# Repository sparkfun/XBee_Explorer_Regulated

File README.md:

XBee Explorer Regulated
=======================

*[XBee Explorer Regulated (WRL-11373)](https://www.sparkfun.com/products/11373)*
 
 This Explorer regulates 5V serial signals to 3.3V to enable communication with the XBee modules.
 This model works with all XBee modules, including Series 1 and 2, standard and Pro versions. 
 
Repository Contents
-------------------

* **/Hardware** - All Eagle design files (.brd, .sch)

License Information
-------------------
The hardware is released under [Creative Commons ShareAlike 4.0 International](https://creativecommons.org/licenses/by-sa/4.0/).
The code is beerware; if you see me (or any other SparkFun employee) at the local, and you've found our code helpful, please buy us a round!

Distributed as-is; no warranty is given.

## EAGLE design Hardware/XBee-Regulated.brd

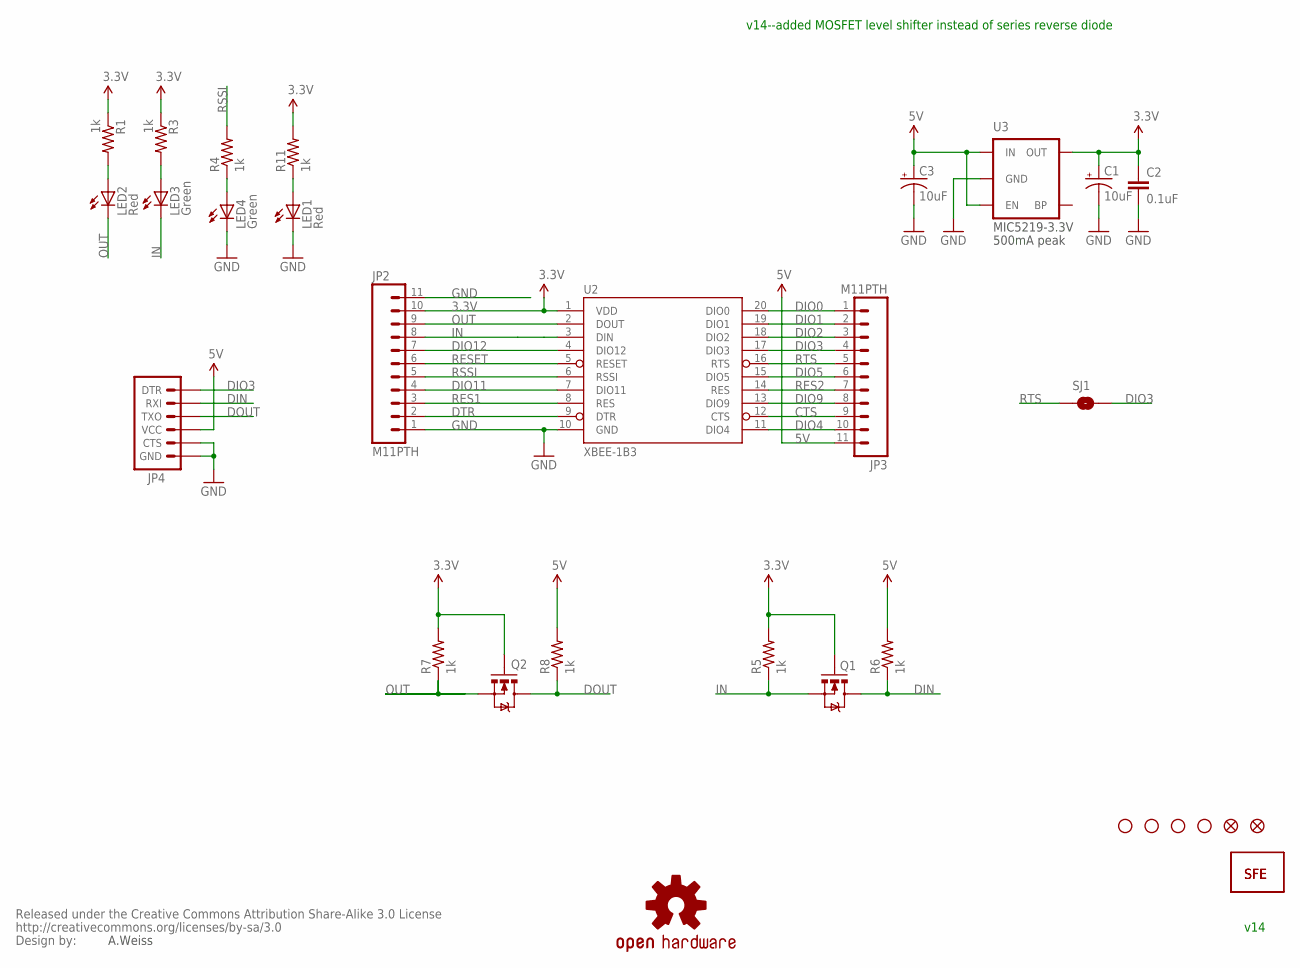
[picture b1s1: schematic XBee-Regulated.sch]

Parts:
C1, C3: 10uF; EIA3216
C2: 0.1uF; 0402-CAP
JP2, JP3: M11PTH; 1X11
JP4: ARDUINO_SERIAL_PROGRAMPTH; 1X06
LED1, LED2: Red; LED-0603
LED3, LED4: Green; LED-0603
Q1, Q2: MOSFET-NCHANNELSMD; SOT23-3
R1, R3, R4, R5, R6, R7, R8, R11: 1k; 0402-RES
SJ1: SOLDERJUMPERNO; SJ_2S-NO
U2: XBEE-1B3; XBEE-SMD
U3: V_REG_LDOSMD; SOT23-5
U$1: LOGO-SFESK; SFE-LOGO-FLAME
U$3: OSHW-LOGOS; OSHW-LOGO-S
U$4: LOGO-SFENEW; SFE-NEW-WEBLOGO
U$5, U$9, U$10, U$11: STAND-OFF
U$7, U$16: FIDUCIAL1X2; FIDUCIAL-1X2
U$8: CREATIVE_COMMONS

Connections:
3.3V: C1.A (+), C2.1, JP2.10, Q1.1 (G), Q2.1 (G), R1.1, R3.1, R5.2, R7.2, R11.2, U2.1 (VDD), U3.5 (OUT)
5V: C3.A (+), JP3.11, JP4.4 (VCC), R6.2, R8.2, U3.1 (IN), U3.3 (EN)
CTS: JP3.9, U2.12 (CTS)
DIN: JP4.2 (RXI), Q1.3 (D), R6.1
DIO0: JP3.1, U2.20 (DIO0)
DIO1: JP3.2, U2.19 (DIO1)
DIO2: JP3.3, U2.18 (DIO2)
DIO3: JP3.4, JP4.1 (DTR), SJ1.2, U2.17 (DIO3)
DIO4: JP3.10, U2.11 (DIO4)
DIO5: JP3.6, U2.15 (DIO5)
DIO9: JP3.8, U2.13 (DIO9)
DIO11: JP2.4, U2.7 (DIO11)
DIO12: JP2.7, U2.4 (DIO12)
DOUT: JP4.3 (TXO), Q2.3 (D), R8.1
DTR: JP2.2, U2.9 (DTR)
GND: C1.C (-), C2.2, C3.C (-), JP2.1, JP2.11, JP4.5 (CTS), JP4.6 (GND), LED1.C, LED4.C, U2.10 (GND), U3.2 (GND)
IN: JP2.8, LED3.C, Q1.2 (S), R5.1, U2.3 (DIN)
unnamed: LED2.A, R1.2
unnamed: LED4.A, R4.1
unnamed: LED3.A, R3.2
unnamed: LED1.A, R11.1
OUT: JP2.9, LED2.C, Q2.2 (S), R7.1, U2.2 (DOUT)
RES1: JP2.3, U2.8 (RES)
RES2: JP3.7, U2.14 (RES)
RESET: JP2.6, U2.5 (RESET)
RSSI: JP2.5, R4.2, U2.6 (RSSI)
RTS: JP3.5, SJ1.1, U2.16 (RTS)

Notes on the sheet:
A.Weiss
v14--added MOSFET level shifter instead of series reverse diode
MIC5219-3.3V
500mA peak
v14

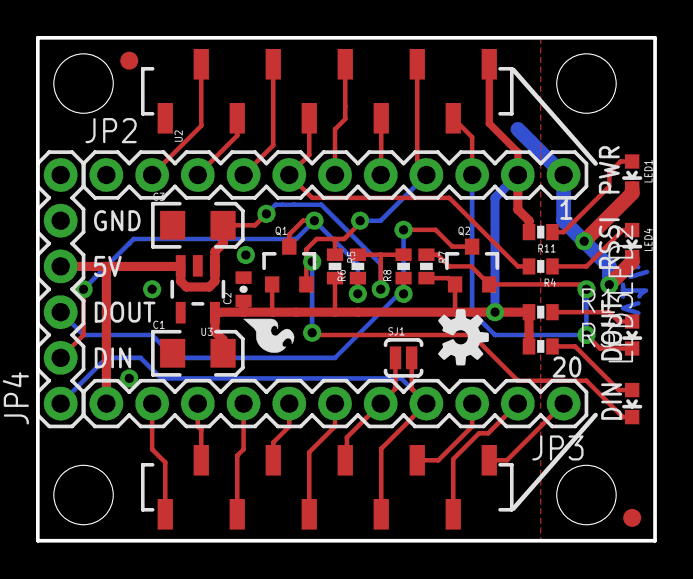
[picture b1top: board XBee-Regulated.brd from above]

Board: 2 copper layers, 34.3 x 27.9 mm, 33 parts (1 on the bottom side), 27 nets.

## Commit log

2014-05-20 Adding hardware files and updating README

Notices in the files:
parts and their libraries:
SparkFun-DiscreteSemi: Licensing: CC v3.0 Share-Alike You are welcome to use this library for commercial purposes.
SparkFun-Aesthetics: Released under the Creative Commons Attribution Share-Alike 3.0 License
SparkFun-Aesthetics: http://creativecommons.org/licenses/by-sa/3.0
